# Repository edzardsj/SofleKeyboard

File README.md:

# Sofle Keyboard

## Internal Notes

 - [ ] Enable microcontroller with USB-C (possibly use a specific uC and redo the breakout on the PCB)
 - [ ] Use a scroll wheel (EVQ-WGD001) instead of a rotary encoder ([reference](https://oshwlab.com/ChristAlix/evqwgd001-roll-encoder_carrier-board_copy]) --- [KiCad model](https://github.com/crides/kleeb/blob/master/switch.pretty/EVQWGD001.kicad_mod))  
and add PCB mounting support
 - [ ] Add drilled holes to the PCB for more sophisticated case designs
 - [ ] Check button positioning + scroll wheel positioning / orientation on printed layout
 
 ## Vanilla docs

Sofle is 6×4+5 keys column-staggered split keyboard with encoder support. Based on [Lily58](https://github.com/kata0510/Lily58), [Corne](https://github.com/foostan/crkbd) and [Helix](https://github.com/MakotoKurauchi/helix) keyboards.

**[For more information and documentation visit https://josefadamcik.github.io/SofleKeyboard/](https://josefadamcik.github.io/SofleKeyboard/)**

SofleKeyboard was created by [Josef Adamcik](https://josef-adamcik.cz/). The motivation and process is covered in following blog-post: [Let me introduce you SofleKeyboard - a split keyboard based on Lily58 and Crkbd](https://josef-adamcik.cz/electronics/let-me-introduce-you-sofle-keyboard-split-keyboard-based-on-lily58.html)

Sofle RGB was contributed by [Dane Evans](https://github.com/DaneEvans).

Sofle soldered was contributed by [kb-elmo](https://github.com/kb-elmo)

## Firmware 

Sofle uses [QMK firmware](https://qmk.fm/)

## Default layout 

## Images of keyboard

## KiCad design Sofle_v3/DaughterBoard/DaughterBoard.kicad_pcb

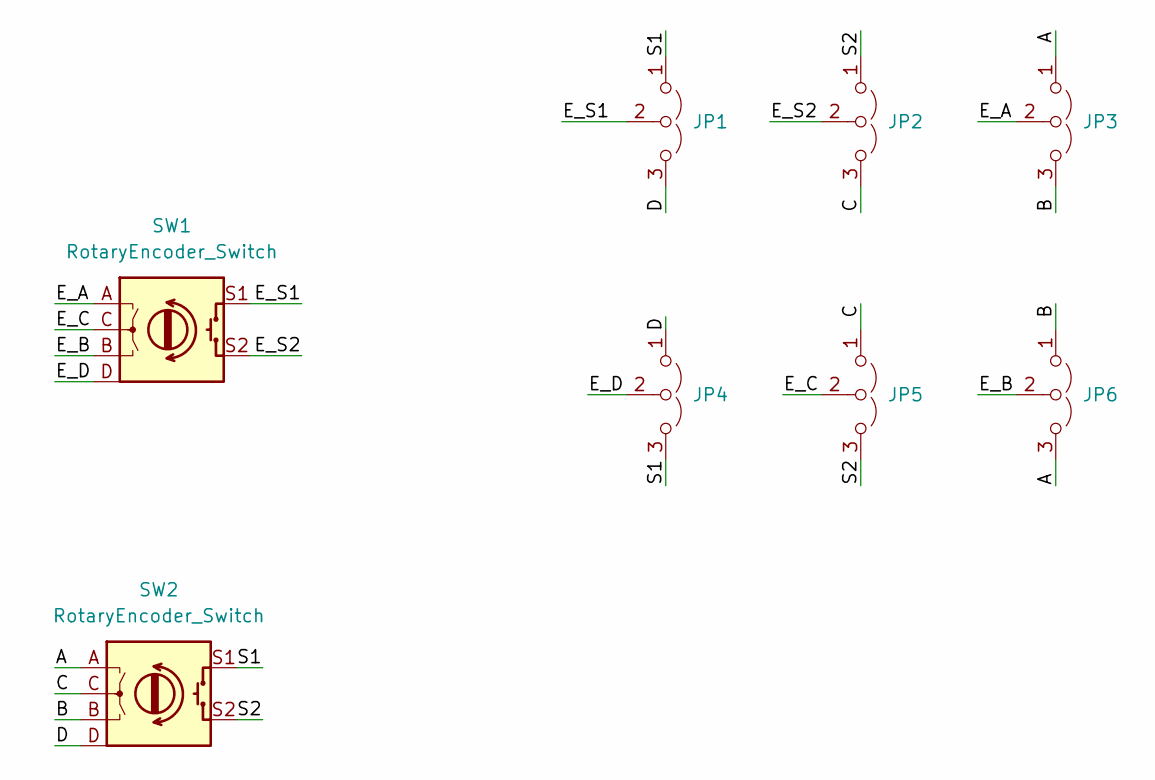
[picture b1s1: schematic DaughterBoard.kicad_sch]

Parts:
JP1, JP2, JP3, JP4, JP5, JP6: Jumper_3_Open; SolderJumper-3_P1.3mm_Open_Pad1.0x1.5mm
SW1: RotaryEncoder_Switch; EVQWGD001
SW2: RotaryEncoder_Switch; EVQWGD001_DaughterBoard_only

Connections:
/A: JP3.1 (A), JP6.3 (B), SW2.A
/B: JP3.3 (B), JP6.1 (A), SW2.B
/C: JP2.3 (B), JP5.1 (A), SW2.C
/D: JP1.3 (B), JP4.1 (A), SW2.D
/E_A: JP3.2 (C), SW1.A
/E_B: JP6.2 (C), SW1.B
/E_C: JP5.2 (C), SW1.C
/E_D: JP4.2 (C), SW1.D
/E_S1: JP1.2 (C), SW1.S1
/E_S2: JP2.2 (C), SW1.S2
/S1: JP1.1 (A), JP4.3 (B), SW2.S1
/S2: JP2.1 (A), JP5.3 (B), SW2.S2

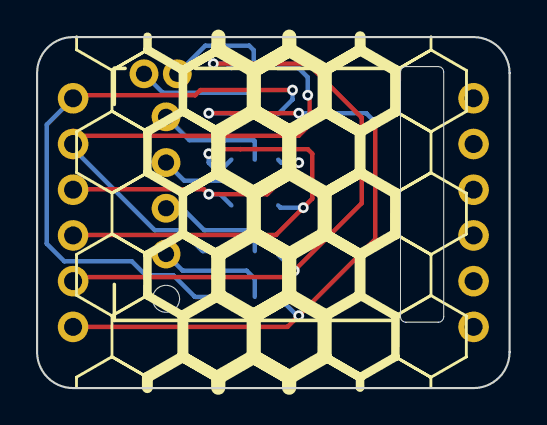
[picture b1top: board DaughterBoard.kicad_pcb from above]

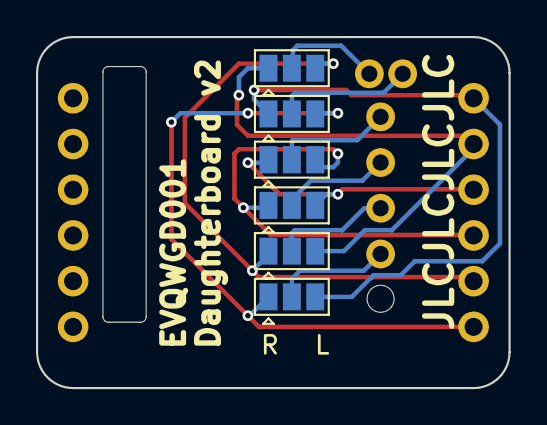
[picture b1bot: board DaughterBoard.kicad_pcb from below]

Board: 2 copper layers, 26.2 x 19.5 mm, 8 parts (6 on the bottom side), 12 nets.

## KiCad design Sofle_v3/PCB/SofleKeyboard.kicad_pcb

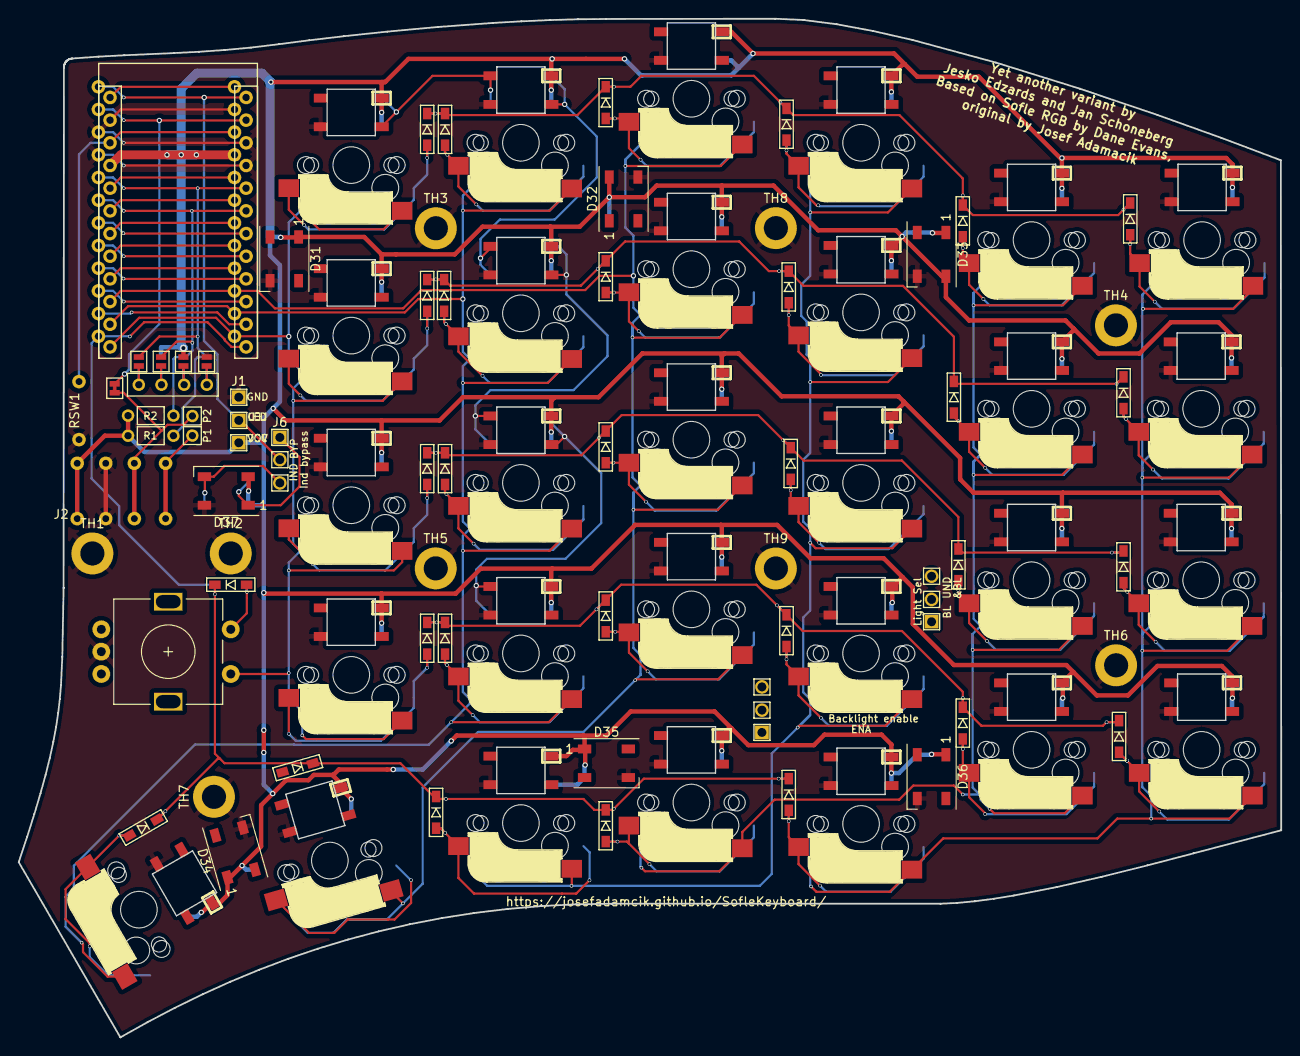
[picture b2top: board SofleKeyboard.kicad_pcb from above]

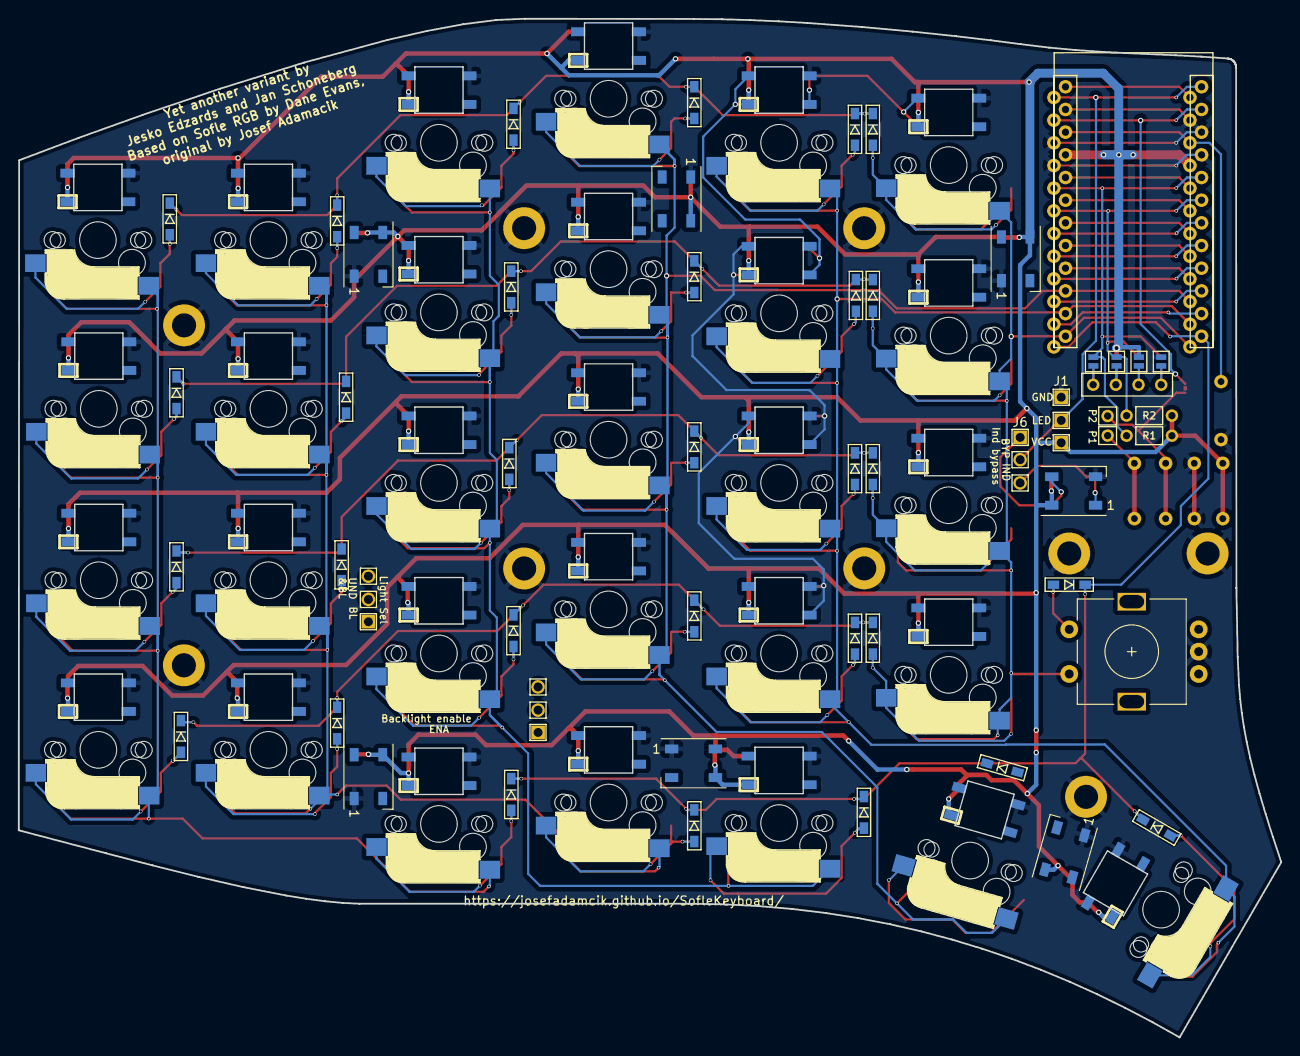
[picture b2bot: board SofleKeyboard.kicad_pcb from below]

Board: 2 copper layers, 141.4 x 114.1 mm, 97 parts (4 on the bottom side), 94 nets.

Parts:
D1, D2, D3, D4, D5, D6, D7, D8, D9, D10, D11, D12, D13, D14, D15, D16, D17, D18, D19, D20, D21, D22, D23, D24, D25, D26, D27, D28, D29, D30: D; crkbd-diode
D31, D32, D33, D34, D35, D36, D37: LED_sk2812_SM; LED_WS2812B_TwoSided
J1: LED
J2: 4PIN; WM2211210044
J3: OLED; OLED_4Pin
J4: key leds; 3x1header
J5: backlight sel; 3x1header
J6: indicator bypass; 3x1header
JP1, JP2, JP3, JP4, JP5, JP6, JP7, JP8: Jumper_NO_Small; Jumper
P1, P2: i2c_pin; 1pin_conn
R1, R2: R; RESISTOR_mini
RSW1: SW_RST; TPS635-1B43D
SW1, SW2, SW3, SW4, SW5, SW6, SW7, SW8, SW9, SW10, SW11, SW12, SW13, SW14, SW15, SW16, SW17, SW18, SW19, SW20, SW21, SW22, SW23, SW24, SW26, SW27, SW28, SW29, SW30: SW_PUSH-MX_W_LED; 5050_and_cherry
SW25: Rotary_Encoder_Switch; RotaryEncoder_Alps_EC11E-Switch_Vertical_H20mm-keebio_modif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
TH1, TH2, TH3, TH4, TH5, TH6, TH7, TH8, TH9: HOLE; MountingHole_2.7mm_M2.5_DIN965_Pad
U1: ProMicro
W1: jumper; jumper_data

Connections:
/SW1_D: D1.2 (A), SW1.5
/SW2_D: D2.2 (A), SW2.5
/SW3_D: D3.2 (A), SW3.5
/SW4_D: D4.2 (A), SW4.5
/SW5_D: D5.2 (A), SW5.5
/SW6_D: D6.2 (A), SW6.5
/SW7_D: D7.2 (A), SW7.5
/SW8_D: D8.2 (A), SW8.5
/SW9_D: D9.2 (A), SW9.5
/SW10_D: D10.2 (A), SW10.5
/SW11_D: D11.2 (A), SW11.5
/SW12_D: D12.2 (A), SW12.5
/SW13_D: D13.2 (A), SW13.5
/SW14_D: D14.2 (A), SW14.5
/SW15_D: D15.2 (A), SW15.5
/SW16_D: D16.2 (A), SW16.5
/SW17_D: D17.2 (A), SW17.5
/SW18_D: D18.2 (A), SW18.5
/SW19_D: D19.2 (A), SW19.5
/SW20_D: D20.2 (A), SW20.5
/SW21_D: D21.2 (A), SW21.5
/SW22_D: D22.2 (A), SW22.5
/SW23_D: D23.2 (A), SW23.5
/SW24_D: D24.2 (A), SW24.5
/SW25B: D25.2 (A), SW25.S2
/SW26_D: D26.2 (A), SW26.5
/SW27_D: D27.2 (A), SW27.5
/SW28_D: D28.2 (A), SW28.5
/SW29_D: D29.2 (A), SW29.5
/SW30_D: D30.2 (A), SW30.5
/backlight: J4.1, J5.1, SW30.2 (DIN)
/i2c_c: J2.4, P1.1
/i2c_d: J2.3, P2.1, W1.2
/underglow: D33.4 (DIN), J4.3
DATA: U1.2 (RX(PD2)), W1.1
ENCA: SW25.A, U1.20 (A3(PF4))
ENCB: SW25.B, U1.19 (A2(PF5))
GND: D31.3 (VSS), D32.3 (VSS), D33.3 (VSS), D34.3 (VSS), D35.3 (VSS), D36.3 (VSS), D37.4 (DIN), J1.3, J2.2, JP1.2, JP8.2, RSW1.1, SW1.3 (VSS), SW2.3 (VSS), SW3.3 (VSS), SW4.3 (VSS), SW5.3 (VSS), SW6.3 (VSS), SW7.3 (VSS), SW8.3 (VSS), SW9.3 (VSS), SW10.3 (VSS), SW11.3 (VSS), SW12.3 (VSS), SW13.3 (VSS), SW14.3 (VSS), SW15.3 (VSS), SW16.3 (VSS), SW17.3 (VSS), SW18.3 (VSS), SW19.3 (VSS), SW20.3 (VSS), SW21.3 (VSS), SW22.3 (VSS), SW23.3 (VSS), SW24.3 (VSS), SW25.C, SW26.3 (VSS), SW27.3 (VSS), SW28.3 (VSS), SW29.3 (VSS), SW30.3 (VSS), TH1.1, TH2.1, TH3.1, TH4.1, TH5.1, TH6.1, TH7.1, TH8.1, TH9.1, U1.3 (GND), U1.4 (GND), U1.23 (GND)
LED: J1.2, J6.2, U1.1 (TX(PD3))
unnamed: D31.2 (DOUT), D34.4 (DIN)
unnamed: D31.4 (DIN), D32.2 (DOUT)
unnamed: D32.4 (DIN), D33.2 (DOUT)
unnamed: D34.2 (DOUT), D35.4 (DIN)
unnamed: D35.2 (DOUT), D36.4 (DIN)
unnamed: D36.2 (DOUT), J5.2
unnamed: D37.3 (VSS), J6.3
unnamed: J3.1, JP4.1, JP8.1
unnamed: J3.2, JP3.1, JP7.1
unnamed: J3.3, JP2.1, JP6.1
unnamed: J3.4, JP1.1, JP5.1
unnamed: SW1.2 (DIN), SW2.4 (DOUT)
unnamed: SW1.4 (DOUT), SW7.2 (DIN)
unnamed: SW2.2 (DIN), SW8.4 (DOUT)
unnamed: SW3.2 (DIN), SW4.4 (DOUT)
unnamed: SW3.4 (DOUT), SW9.2 (DIN)
unnamed: SW5.2 (DIN), SW6.4 (DOUT)
unnamed: SW10.2 (DIN), SW16.4 (DOUT)
unnamed: SW4.2 (DIN), SW10.4 (DOUT)
unnamed: SW5.4 (DOUT), SW11.2 (DIN)
unnamed: SW11.4 (DOUT), SW17.2 (DIN)
unnamed: SW12.2 (DIN), SW18.4 (DOUT)
unnamed: SW6.2 (DIN), SW12.4 (DOUT)
unnamed: SW7.4 (DOUT), SW13.2 (DIN)
unnamed: SW13.4 (DOUT), SW19.2 (DIN)
unnamed: SW14.2 (DIN), SW20.4 (DOUT)
unnamed: SW8.2 (DIN), SW14.4 (DOUT)
unnamed: SW9.4 (DOUT), SW15.2 (DIN)
unnamed: SW15.4 (DOUT), SW21.2 (DIN)
unnamed: SW16.2 (DIN), SW22.4 (DOUT)
unnamed: SW17.4 (DOUT), SW23.2 (DIN)
unnamed: SW18.2 (DIN), SW24.4 (DOUT)
unnamed: SW20.2 (DIN), SW26.4 (DOUT)
unnamed: SW21.4 (DOUT), SW27.2 (DIN)
unnamed: SW22.2 (DIN), SW28.4 (DOUT)
unnamed: SW23.4 (DOUT), SW29.2 (DIN)
unnamed: SW24.2 (DIN), SW30.4 (DOUT)
unnamed: SW26.2 (DIN), SW27.4 (DOUT)
unnamed: SW28.2 (DIN), SW29.4 (DOUT)
RESET: RSW1.2, U1.22 (RST)
SCL: JP3.2, JP6.2, R2.2, U1.6 (SCL(PD0))
SDA: JP4.2, JP5.2, R1.2, U1.5 (SDA(PD1))
VCC: D31.1 (VDD), D32.1 (VDD), D33.1 (VDD), D34.1 (VDD), D35.1 (VDD), D36.1 (VDD), D37.2 (DOUT), J1.1, J2.1, JP2.2, JP7.2, R1.1, R2.1, SW1.1 (VDD), SW2.1 (VDD), SW3.1 (VDD), SW4.1 (VDD), SW5.1 (VDD), SW6.1 (VDD), SW7.1 (VDD), SW8.1 (VDD), SW9.1 (VDD), SW10.1 (VDD), SW11.1 (VDD), SW12.1 (VDD), SW13.1 (VDD), SW14.1 (VDD), SW15.1 (VDD), SW16.1 (VDD), SW17.1 (VDD), SW18.1 (VDD), SW19.1 (VDD), SW20.1 (VDD), SW21.1 (VDD), SW22.1 (VDD), SW23.1 (VDD), SW24.1 (VDD), SW26.1 (VDD), SW27.1 (VDD), SW28.1 (VDD), SW29.1 (VDD), SW30.1 (VDD), U1.21 (VCC)
col0: SW6.6, SW12.6, SW18.6, SW24.6, SW30.6, U1.18 (A1(PF6))
col1: SW5.6, SW11.6, SW17.6, SW23.6, SW29.6, U1.17 (A0(PF7))
col2: SW4.6, SW10.6, SW16.6, SW22.6, SW28.6, U1.16 (D15(PB1))
col3: SW3.6, SW9.6, SW15.6, SW21.6, SW27.6, U1.15 (D14(PB3))
col4: SW2.6, SW8.6, SW14.6, SW20.6, SW26.6, U1.14 (D16(PB2))
col5: SW1.6, SW7.6, SW13.6, SW19.6, SW25.S1, U1.13 (D10(PB6))
lights: D37.1 (VDD), J4.2, J6.1
row0: D1.1 (K), D2.1 (K), D3.1 (K), D4.1 (K), D5.1 (K), D6.1 (K), U1.8 (D5(PC6))
row1: D7.1 (K), D8.1 (K), D9.1 (K), D10.1 (K), D11.1 (K), D12.1 (K), U1.9 (D6(PD7))
row2: D13.1 (K), D14.1 (K), D15.1 (K), D16.1 (K), D17.1 (K), D18.1 (K), U1.10 (D7(PE6))
row3: D19.1 (K), D20.1 (K), D21.1 (K), D22.1 (K), D23.1 (K), D24.1 (K), U1.11 (D8(PB4))
row4: D25.1 (K), D26.1 (K), D27.1 (K), D28.1 (K), D29.1 (K), D30.1 (K), U1.12 (D9(PB5))

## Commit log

2022-10-17 docs: udate readme for custom TODOs
2022-10-17 docs: update EVQWGD001 reference
2022-10-26 [feat] Removed temp files and added temp files to gitignore
2022-10-26 [chore] Replaced old .pro with KiCad v6 .kicad_pro file
2022-10-26 Added RP2040 schematic and footprint
2022-10-26 Current progress in RP2040 design
2022-10-26 Added EVQWGD001.kicad_mod from github.com/crides/kleeb
2022-10-27 RP2040 schematic: - Added Reset and Boot button - Added Crystal - Added Flash - Added (optional) LED level shifter - Rearanged schematic
    Main schematic:
    - Imported Pins from rp2040 schematic
    - Replaced VCC with VBUS representing USB voltage
2022-10-28 Added some footprints
2022-11-15 design: add sofle RGB v3
2022-12-08 design: base sofle RGB v3 pcb
2022-12-09 design: Added more footprints and symbols
2022-12-09 design: routing and schematic beatifications
2022-12-12 design: routing without drc complete;
    Daughterboard for scroll not started yet
2022-12-12 design: added/changed daughterboard footprint also added jumpers for rotatry encoder side switch
2022-12-18 design: minor orientation change added daughterboard first drc checks
2022-12-20 design final drc adjustments and added a qr code
2022-12-20 design rotated outer thumb key
2022-12-26 design: add template for Silkscreen design
2022-12-29 design: removed cutout for daughter board + increased led distance
2023-01-03 design: add left half for silkscreen design
2023-01-05 design: Moved uC down to not overlap edge cut Swapped wron DataIn with DataOut for WS2812B
2023-01-08 design: Daughter board - Redesign and added pcb project - Some 3d model shenanigans
2023-01-08 design: daughter board update
2023-01-10 design: remove creators credit
    moved to custom silkscreen design
2023-01-15 design: replaced staggered uC design with solder jumpers
2023-01-16 design: moved uC board 1mm down to make sure it does not stick out
2023-01-18 design(svg): finalize silkscreen design
2023-01-18 design: minor silkscreen corrections
2023-01-18 design: add custom back & front silkscreen
2023-01-18 chore: cleanup of svg files
2023-01-18 design: add custom silkscreen design to main PCB
2023-01-21 production files added
2023-01-21 design: add silksceen design to daughterboard
2023-02-26 Design: Fixed daughterboard pinout/Made it configurable
2023-04-25 chore: add blank cheat sheet
    for learning the new layout
2023-04-25 fea: add firmware modifications for via
    this needs to be transferred to a qmk-via fork later on
2023-05-14 fix: added adapter board for screwed up footprint
2023-08-05 [chore] Removed outdates gerber files.
    The gerber files should be considered binaries and do not need to be
    tracked in the git repository since they can easily be generated with
    the correct settings according to the PCB manifacturer of choice.
2023-08-05 [fix] Fixed wrong Footprint for reset button and klinken connector
    Additionally updated files to new KiCad Version 7
2023-08-05 [chore] Updated Project files to new KiCad version
2023-08-05 [Fix] Fixed wrong wiring of Daughter board
    To be precice, the main pcb has a wrong layout but it is cheaper
    and easier to fix the wiring on the daughter board. This is now
    how it alaways was meant to be ;)
2023-08-05 [Fix] Wrong inidicator for first pin
    This should fix issue #1
